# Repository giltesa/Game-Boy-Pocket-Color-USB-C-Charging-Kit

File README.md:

# Game Boy Pocket/Color: USB-C Charging Kit (GB2)

The **Game Boy Pocket/Color: USB-C Charging Kit**, or **GB2** as I like to call it, is a circuit that replaces the original power board of the **Game Boy Pocket** and **Game Boy Color**.

This circuit is a **multi-device** and versatile board with **multiple installation options**. This means that **this kit can be used for both Game Boy models**, and you can decide whether you want to **power your console with AA/AAA** batteries **or a rechargeable li-ion battery**. You can also choose between using the **original 2.5mm DC power connector** **or replacing it with a USB-C**. Additionally, you have **the option to install a light board that will indicate the status of the console and battery**, all from the original hole on the console, next to the screen.

### FEATURES

*   Exact **shape for Game Boy Pocket & Game Boy Color**.
*   **Power DC converter** of **5V** output. **(1)**
*   **External power** through **2.5mm DC jack** or **USB-C.** **(2)**
*   **Li-Ion battery charger** with overvoltage and undervoltage protection. **(2)**
*   **Safe charge and play**.
*   **Integrated LED indicators** on the main board, next to the battery connector for charging battery (red) and full battery (green). It can be disabled by the jumper SJ1.
*   **External LED indicators** board for playing (white), charging battery (red) and full battery (green). Optional installation.

**(1)** Provides stable power to your Game Boy, IPS screen, and flash card. However, it doesn't supply the -19v rail, which means the stock screen or GBP IPS screen, which adjusts brightness through the contrast wheel, will not be able to change the brightness level and will remain at its maximum level.

**(2)** The USB-C and li-ion battery require trimming of the shell. Please refer to the PDF installation manual for more information.

https://www.youtube.com/watch?v=UszhrSf1U5U

## Would you like it?

https://shop.giltesa.com/product/game-boy-pocket-color-usb-c-charging-kit/

## More

- [giltesa.com](https://giltesa.com "giltesa.com")
- [twitter.com](https://twitter.com/giltesa "twitter.com")

## License

This project is licensed under a **Creative Commons** license:
**[Attribution-NonCommercial-ShareAlike 4.0 International (CC BY-NC-SA 4.0) ](https://creativecommons.org/licenses/by-nc-sa/4.0/)**

Check the [LICENSE.md](LICENSE.md) for more information.

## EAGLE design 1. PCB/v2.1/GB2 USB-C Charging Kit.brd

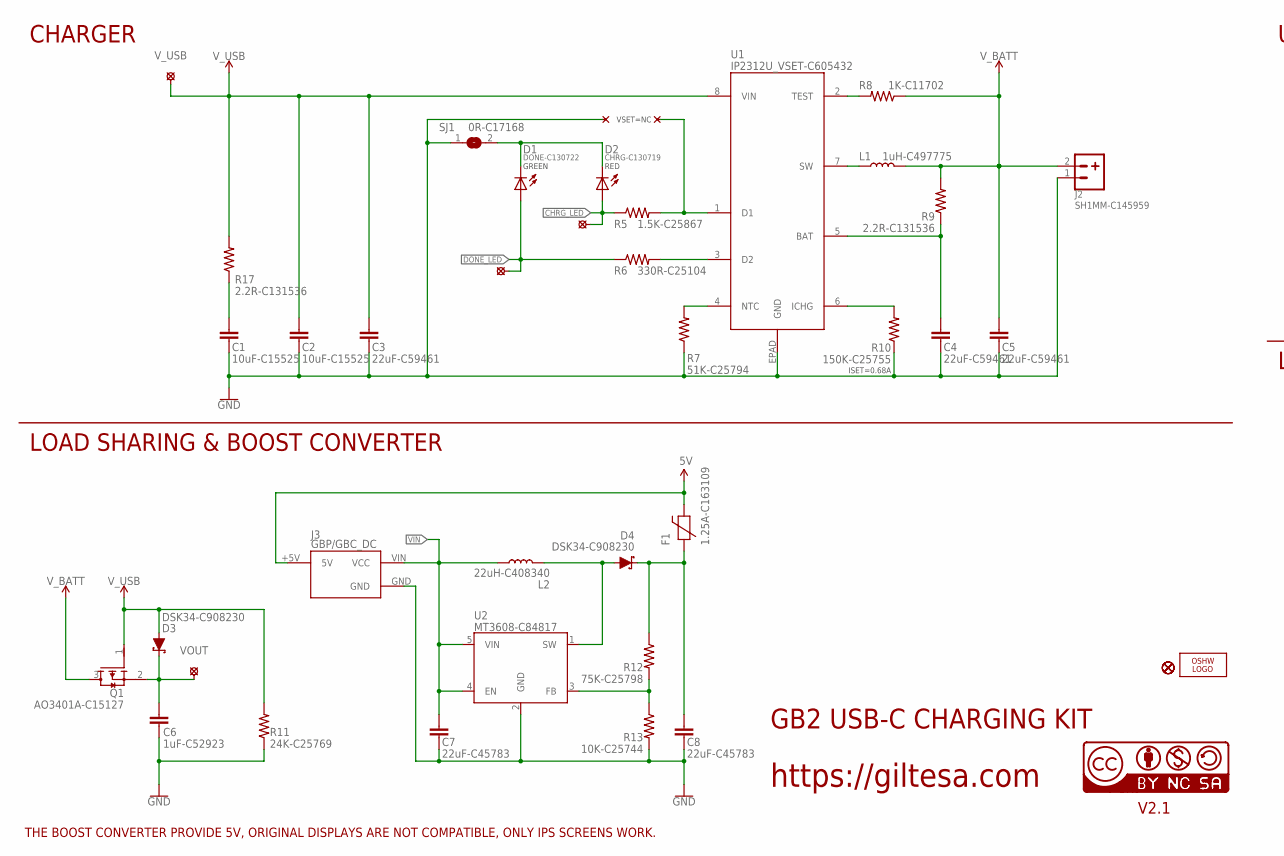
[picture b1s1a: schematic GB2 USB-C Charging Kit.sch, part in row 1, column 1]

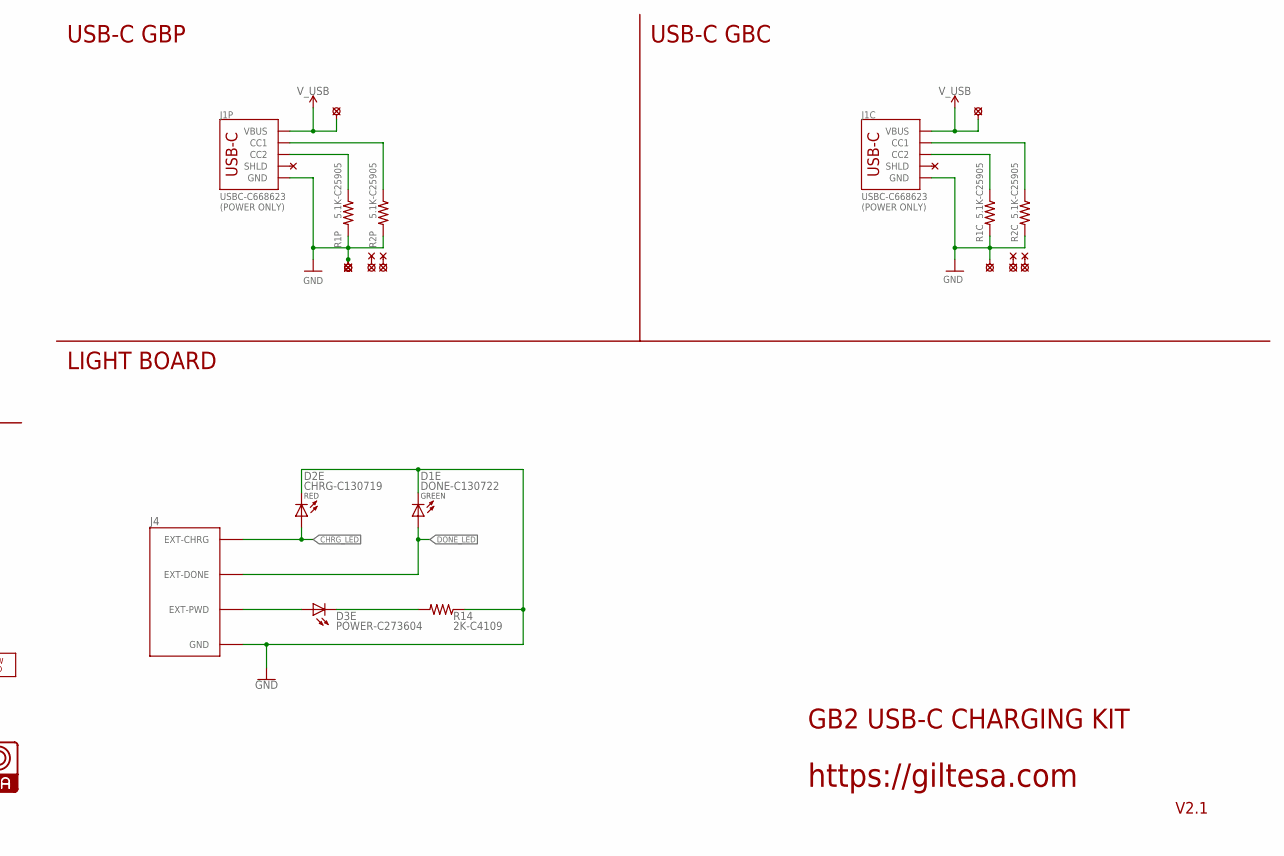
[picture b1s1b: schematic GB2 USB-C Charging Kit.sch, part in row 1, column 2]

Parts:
C1, C2: 10uF-C15525; C0402_S
C3, C4, C5: 22uF-C59461; C0603_S
C6: 1uF-C52923; C0402_S
C7, C8: 22uF-C45783; C0805_S
D1, D1E: DONE-C130722; L0402
D2, D2E: CHRG-C130719; L0402
D3, D4: DSK34-C908230; SOD-123FL
D3E: POWER-C273604; L0402
F1: 1.25A-C163109; F0603_S
FD1, FD2, FD3: FIDUCIALUFIDUCIAL; FIDUCIAL-MICRO
J1C, J1P: USBC-C668623; USB-C_6P
J2: SH1MM-C145959; JST-2-1MM-SMD_TOP
J3: GBP/GBC_DC; GB2_DC-DC
J4: GB2_LED
L1: 1uH-C497775; PSPMAA0402
L2: 22uH-C408340; PSPMAA0402
LOGO1: OSHW_LOGO_FILLX0150-NT; OSHW_FILLX150_NOTEXT
Q1: AO3401A-C15127; SOT23-3_S
R1C, R1P, R2C, R2P: 5.1K-C25905; R0402
R5: 1.5K-C25867; R0402
R6: 330R-C25104; R0402
R7: 51K-C25794; R0402
R8: 1K-C11702; R0402
R9, R17: 2.2R-C131536; R0402
R10: 150K-C25755; R0402
R11: 24K-C25769; R0402
R12: 75K-C25798; R0402
R13: 10K-C25744; R0402
R14: 2K-C4109; R0402
SJ1: 0R-C17168; JUMPER-SMD_0402
U1: IP2312U_VSET-C605432; IP2312
U2: MT3608-C84817; SOT-23-6
U$2, U$11, U$15, U$19, U$25, U$33: PAD_1.1
U$13: CC-NC-BCNIX; CC-NC-B_NIX
U$20, U$21: SOLDER_PAD-1.7; SOLDER_PAD_1.7
U$23: VOUT; PAD_0.8
U$24: V_USB; PAD_0.8
U$26, U$27: SOLDER_PAD-2.0; SOLDER_PAD_2.0
U$32: SOLDER_PAD-2.5; SOLDER_PAD_2.5

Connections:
5V: F1.2, J3.+5V (5V)
CHRG_LED: D2.A, D2E.A, J4.EXT-CHRG, R5.1, U$21.P$1
DONE_LED: D1.A, D1E.A, J4.EXT-DONE, R6.1, U$20.P$1
GND: C1.1, C2.1, C3.1, C4.1, C5.1, C6.2, C7.1, C8.1, D1E.C, D2E.C, J1C.A12-GND (GND), J1C.B12-GND (GND), J1P.A12-GND (GND), J1P.B12-GND (GND), J2.1, J3.GND, J4.GND1 (GND), J4.GND2 (GND), J4.GND3 (GND), J4.GND4 (GND), J4.GND5 (GND), R1C.2, R1P.2, R2C.2, R2P.2, R7.1, R10.1, R11.1, R13.2, R14.1, SJ1.1, U1.EPAD (GND), U2.2 (GND), U$19.P$1, U$26.P$1, U$27.P$1
unnamed: J1C.B5 (CC2), R1C.1
unnamed: J1P.A5 (CC1), R2P.1
unnamed: J1P.B5 (CC2), R1P.1
unnamed: D4.A, L2.P$2 (2), U2.1 (SW)
unnamed: D1.C, D2.C, SJ1.2
unnamed: D3E.A, J4.EXT-PWD, J4.EXT-PWD' (EXT-PWD)
unnamed: D3E.C, R14.2
unnamed: R12.2, R13.1, U2.3 (FB)
unnamed: J1C.A5 (CC1), R2C.1
unnamed: C8.2, D4.C, F1.1, R12.1
unnamed: C4.2, R9.1, U1.5 (BAT)
unnamed: R8.2, U1.2 (TEST)
unnamed: C1.2, R17.1
unnamed: R5.2, U1.1 (D1)
unnamed: R7.2, U1.4 (NTC)
unnamed: R10.2, U1.6 (ICHG)
unnamed: R6.2, U1.3 (D2)
unnamed: L1.P$1 (1), U1.7 (SW)
VCC: C6.1, D3.C, Q1.2 (S), U$23.P$1
VIN: C7.2, J3.VIN (VCC), L2.P$1 (1), U2.4 (EN), U2.5 (VIN)
V_BATT: C5.2, J2.2, L1.P$2 (2), Q1.3 (D), R8.1, R9.2
V_USB: C2.2, C3.2, D3.A, J1C.A9-VBUS (VBUS), J1C.B9-VBUS (VBUS), J1P.A9-VBUS (VBUS), J1P.B9-VBUS (VBUS), Q1.1 (G), R11.2, R17.2, U1.8 (VIN), U$24.P$1, U$25.P$1, U$33.P$1

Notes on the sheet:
(POWER ONLY)
GB2 USB-C CHARGING KIT
https://giltesa.com
V2.1
THE BOOST CONVERTER PROVIDE 5V, ORIGINAL DISPLAYS ARE NOT COMPATIBLE, ONLY IPS SCREENS WORK.
USB-C GBC
CHARGER
LOAD SHARING & BOOST CONVERTER
ISET=0.68A
GREEN
RED
VSET=NC
USB-C GBP
LIGHT BOARD

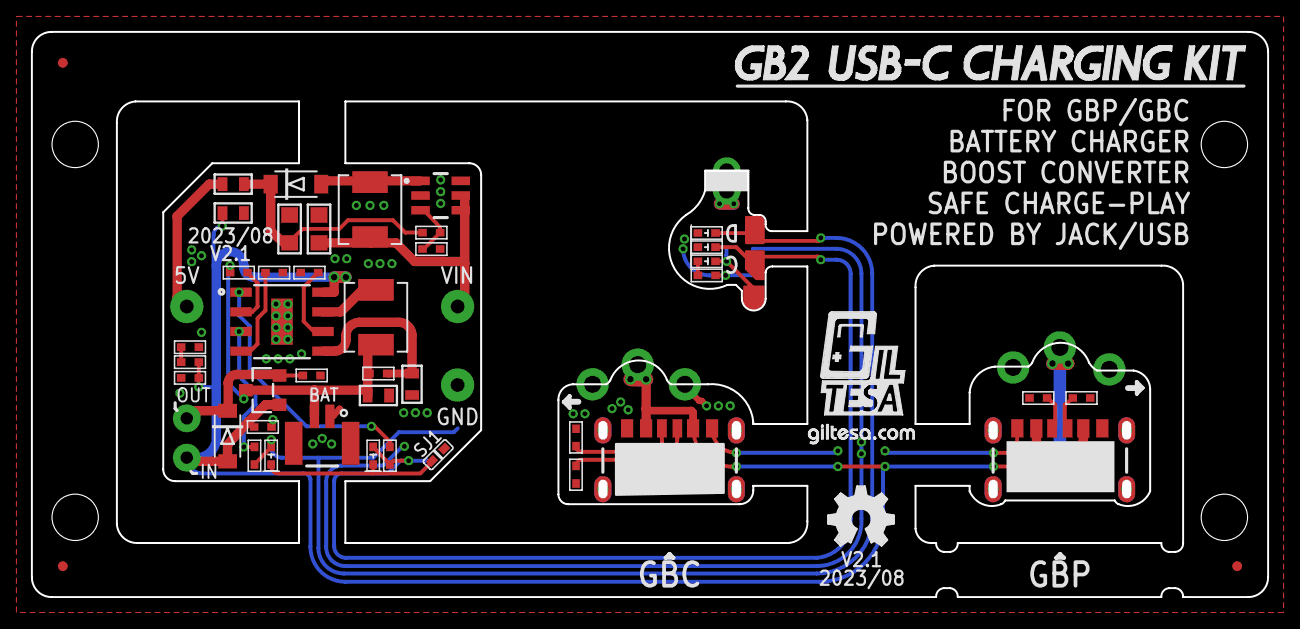
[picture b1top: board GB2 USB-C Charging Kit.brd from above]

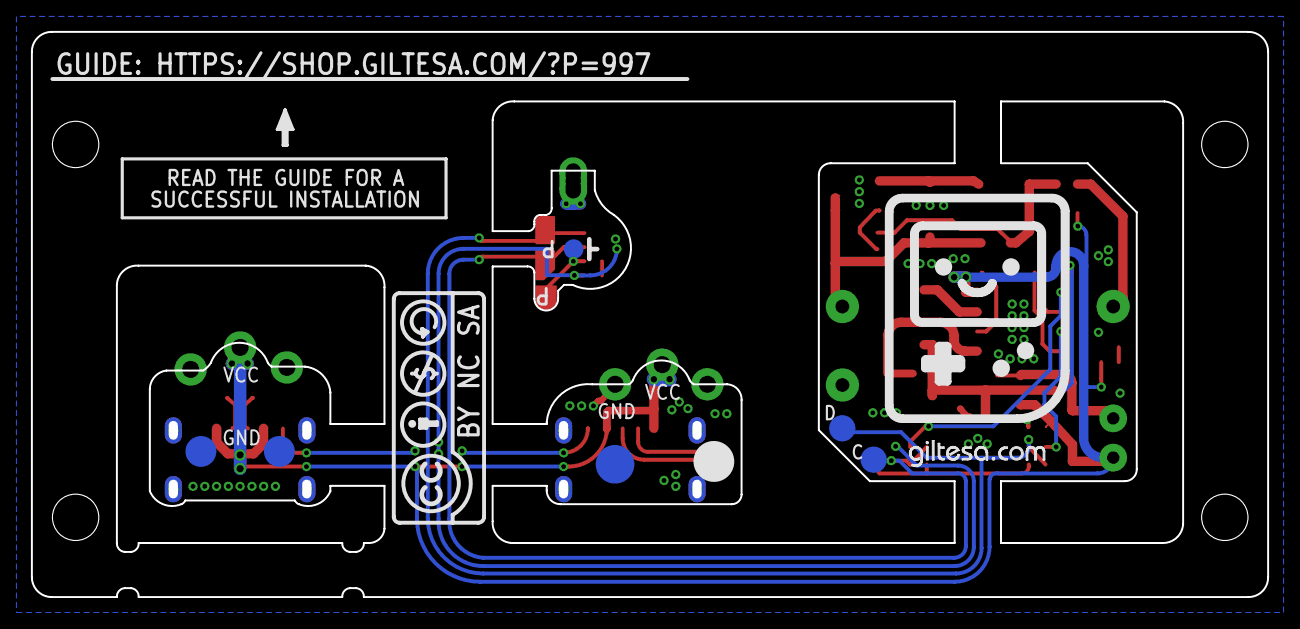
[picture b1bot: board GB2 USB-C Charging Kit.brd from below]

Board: 2 copper layers, 79.5 x 36.1 mm, 66 parts (8 on the bottom side), 26 nets.

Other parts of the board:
U$1: GILTESA_LOGO_MASK_7MM
U$4: GB2_FRAME
U$7: CC-BY-NC-SA15MM; CC-BY-NC-SA_15MM
U$22: GAME_BOY_2
U$28: GILTESA.COM_MASK_7MM
U$29: GILTESA.COM_MASK_9MM

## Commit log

2023-08-21 no message
2024-01-15 v2.1

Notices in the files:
parts and their libraries:
SparkFun-Aesthetics: Licensing: Creative Commons ShareAlike 4.0 International - https://creativecommons.org/licenses/by-sa/4.0
SparkFun: Licensing: CC v3.0 Share-Alike You are welcome to use this library for commercial purposes.
cc-by-nc-sa: All hardware is licensed under the Creative Commons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
